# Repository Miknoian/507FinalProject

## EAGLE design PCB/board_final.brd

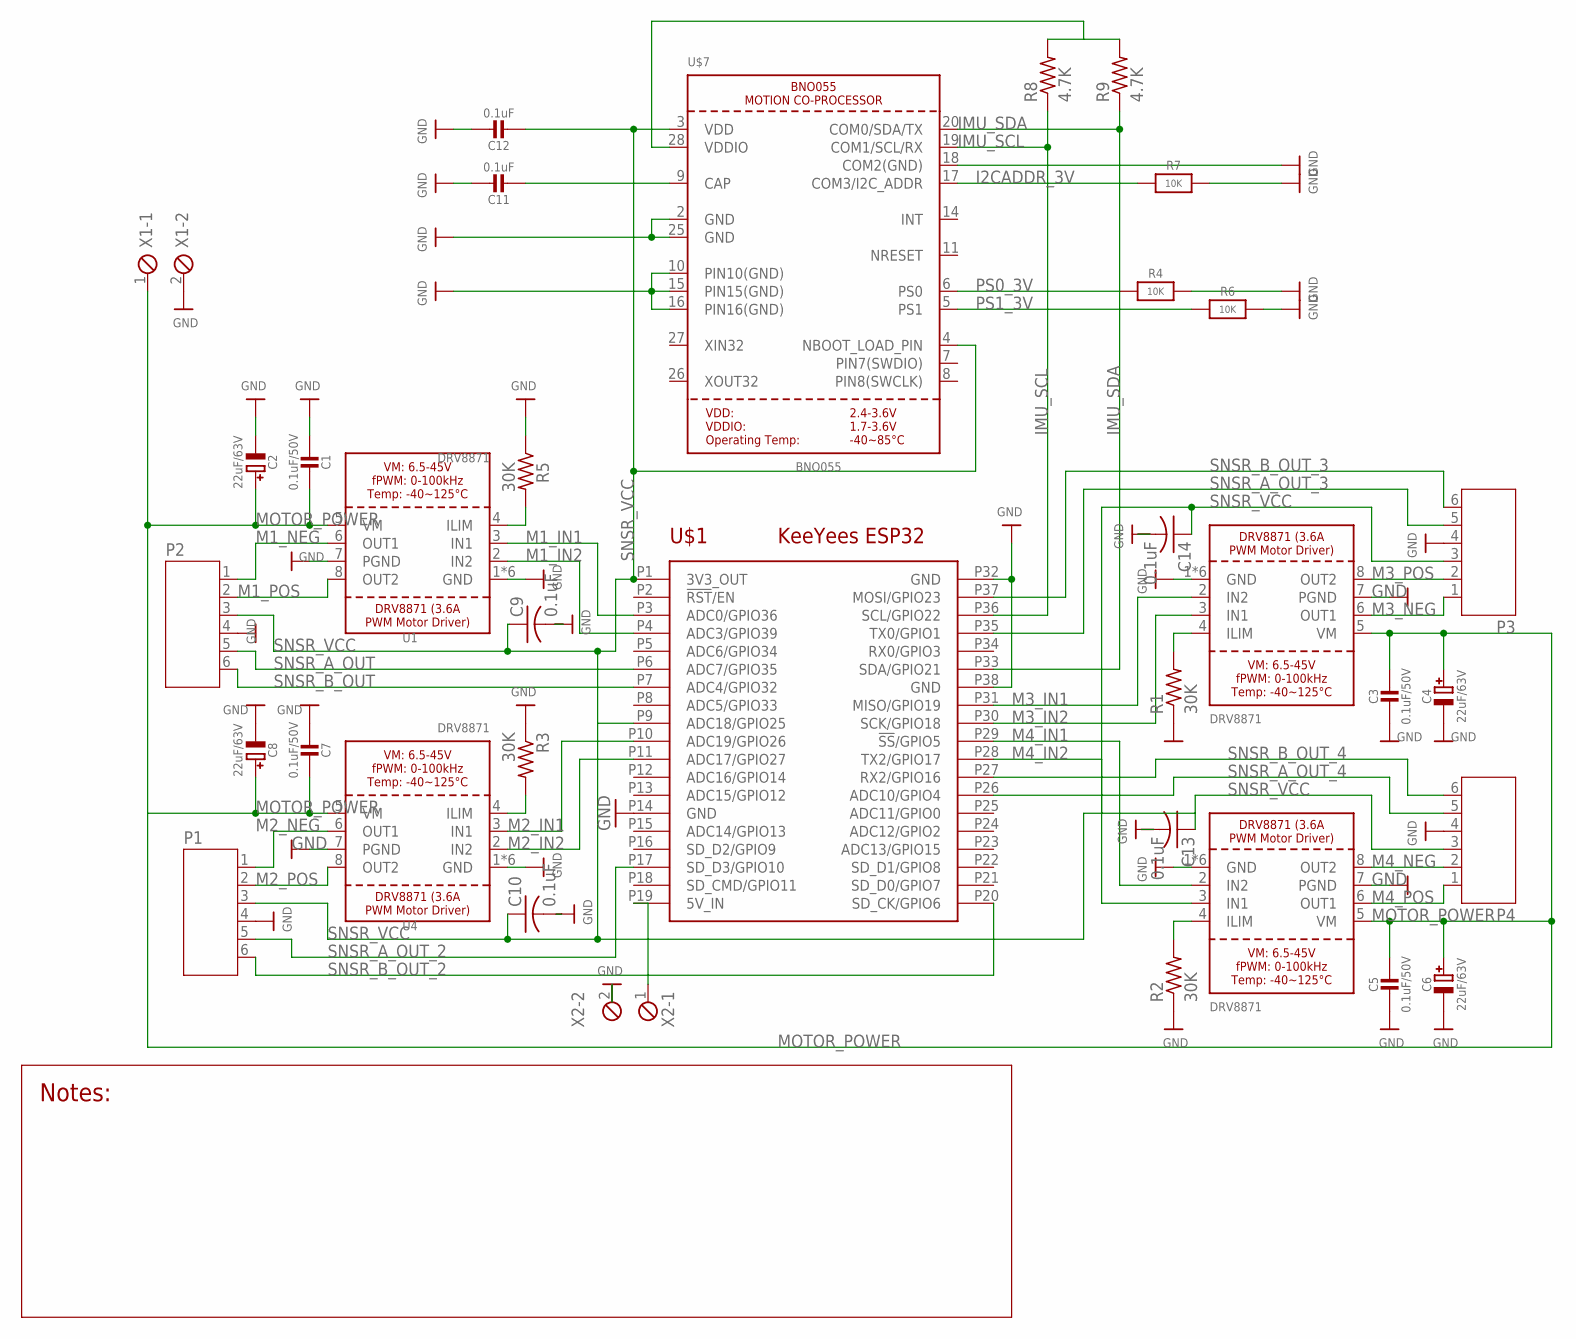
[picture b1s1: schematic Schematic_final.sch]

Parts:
C1, C3, C5, C7: 0.1uF/50V; 0805-NO
C2, C4, C6, C8: 22uF/63V; PANASONIC_D
C9, C10, C13, C14: 0.1uF; C025-030X050
C11: 0.1uF; 0805-NO
C12: 0.1uF; 0805_10MGAP
P1, P2, P3, P4: JST-PH6
R1, R2, R3, R5: 30K; 0805-THM
R4, R6, R7: 10K; 0805-NO
R8, R9: 4.7K; R0805
U1, U2, U3, U4: DRV8871; HSOP8
U$1: KEEYEES_ESP32
U$7: BNO055
X1, X2: SCREWTERM_2P_254; 2POL254

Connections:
ESP_PWR: U$1.P19 (5V_IN), X2.1
GND: C1.2, C2.-, C3.2, C4.-, C5.2, C6.-, C7.2, C8.-, C9.2, C10.2, C11.1, C12.1, C13.2, C14.2, P1.4, P2.4, P3.4, P4.4, R1.1, R2.1, R3.1, R4.2, R5.1, R6.2, R7.2, U1.1 (GND), U1.7 (PGND), U1.GND, U1.P$1 (GND), U1.P$2 (GND), U1.P$3 (GND), U1.P$4 (GND), U2.1 (GND), U2.7 (PGND), U2.GND, U2.P$1 (GND), U2.P$2 (GND), U2.P$3 (GND), U2.P$4 (GND), U3.1 (GND), U3.7 (PGND), U3.GND, U3.P$1 (GND), U3.P$2 (GND), U3.P$3 (GND), U3.P$4 (GND), U4.1 (GND), U4.7 (PGND), U4.GND, U4.P$1 (GND), U4.P$2 (GND), U4.P$3 (GND), U4.P$4 (GND), U$1.P14 (GND), U$1.P32 (GND), U$1.P38 (GND), U$7.2 (GND), U$7.10 (PIN10(GND)), U$7.15 (PIN15(GND)), U$7.16 (PIN16(GND)), U$7.18 (COM2(GND)), U$7.25 (GND), X1.2, X2.2
I2CADDR_3V: R7.1, U$7.17 (COM3/I2C_ADDR)
IMU_SCL: R8.1, U$1.P36 (SCL/GPIO22), U$7.19 (COM1/SCL/RX)
IMU_SDA: R9.1, U$1.P33 (SDA/GPIO21), U$7.20 (COM0/SDA/TX)
M1_IN1: U1.3 (IN1), U$1.P3 (ADC0/GPIO36)
M1_IN2: U1.2 (IN2), U$1.P4 (ADC3/GPIO39)
M1_NEG: P2.1, U1.6 (OUT1)
M1_POS: P2.2, U1.8 (OUT2)
M2_IN1: U4.3 (IN1), U$1.P10 (ADC19/GPIO26)
M2_IN2: U4.2 (IN2), U$1.P11 (ADC17/GPIO27)
M2_NEG: P1.1, U4.6 (OUT1)
M2_POS: P1.2, U4.8 (OUT2)
M3_IN1: U2.2 (IN2), U$1.P31 (MISO/GPIO19)
M3_IN2: U2.3 (IN1), U$1.P30 (SCK/GPIO18)
M3_NEG: P3.1, U2.6 (OUT1)
M3_POS: P3.2, U2.8 (OUT2)
M4_IN1: U3.2 (IN2), U$1.P29 (!SS!/GPIO5)
M4_IN2: U3.3 (IN1), U$1.P28 (TX2/GPIO17)
M4_NEG: P4.2, U3.8 (OUT2)
M4_POS: P4.1, U3.6 (OUT1)
MOTOR_POWER: C1.1, C2.+, C3.1, C4.+, C5.1, C6.+, C7.1, C8.+, U1.5 (VM), U2.5 (VM), U3.5 (VM), U4.5 (VM), X1.1
unnamed: R1.2, U2.4 (ILIM)
unnamed: R2.2, U3.4 (ILIM)
unnamed: R3.2, U4.4 (ILIM)
unnamed: R8.2, R9.2, U$7.28 (VDDIO)
unnamed: C11.2, U$7.9 (CAP)
unnamed: R5.2, U1.4 (ILIM)
PS0_3V: R4.1, U$7.6 (PS0)
PS1_3V: R6.1, U$7.5 (PS1)
SNSR_A_OUT: P2.5, U$1.P6 (ADC7/GPIO35)
SNSR_A_OUT_2: P1.5, U$1.P17 (SD_D3/GPIO10)
SNSR_A_OUT_3: P3.5, U$1.P35 (TX0/GPIO1)
SNSR_A_OUT_4: P4.5, U$1.P26 (ADC10/GPIO4)
SNSR_B_OUT: P2.6, U$1.P7 (ADC4/GPIO32)
SNSR_B_OUT_2: P1.6, U$1.P20 (SD_CK/GPIO6)
SNSR_B_OUT_3: P3.6, U$1.P37 (MOSI/GPIO23)
SNSR_B_OUT_4: P4.6, U$1.P27 (RX2/GPIO16)
SNSR_VCC: C9.1, C10.1, C12.2, C13.1, C14.1, P1.3, P2.3, P3.3, P4.3, U$1.P1 (3V3_OUT), U$7.3 (VDD), U$7.4 (NBOOT_LOAD_PIN)

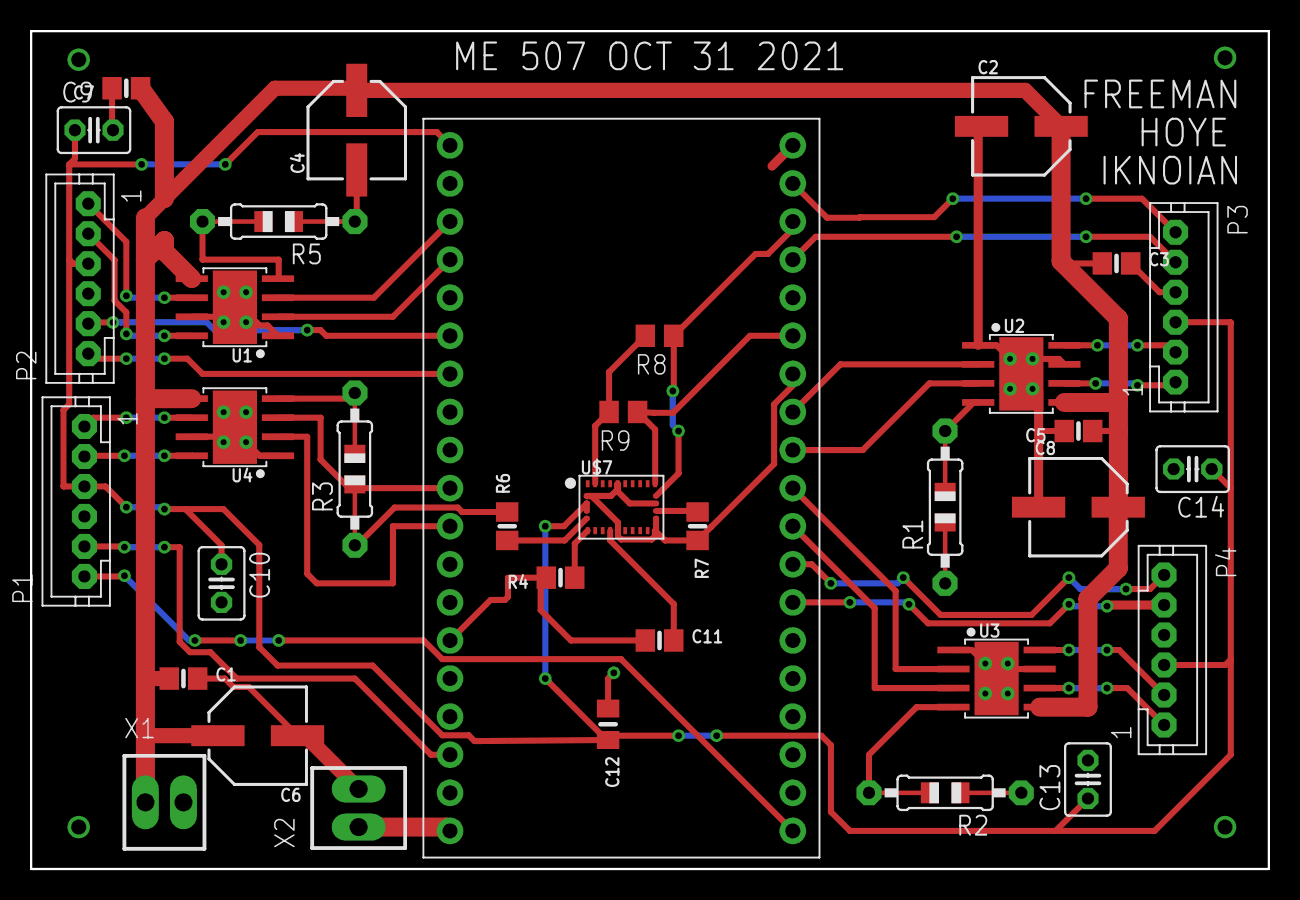
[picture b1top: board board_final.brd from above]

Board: 2 copper layers, 82.5 x 55.9 mm, 35 parts (0 on the bottom side), 39 nets.

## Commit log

2021-11-30 commintinzinng codes
2021-11-30 Update main.cpp
    Important comments
2021-12-01 Added files for the motor driver class
2021-12-01 Small changes to motor class
2021-12-01 added a space to the print line
2021-12-01 WiFi Addition
2021-12-01 First motor task upload
2021-12-01 Controller function with direction functionality.
    Controller function takes a direction input and creates a scaler for the desired speed on each motor. This will then be multiplied by the desired overall nominal speed to get the nominal speed for ea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
2021-12-01 Updated controller function. Still needs work.
2021-12-01 WiFiTasks
2021-12-01 Moved variable declarations
2021-12-01 Added WiFi Task
2021-12-02 Fixed 507 library issues
2021-12-02 Added motor tasks
    Also commented out wifi task because it crashes without the external capacitors.
2021-12-02 Attempting WiFi again
2021-12-02 Made encoder highest priority
2021-12-02 Decreased encoder period
2021-12-02 Added comment about what should be in setup
2021-12-02 Idk but this apparently changed
2021-12-02 Started implementing pulling shares
2021-12-02 WiFi Attempt
2021-12-02 Updated encoder pins
2021-12-02 Changed controller to task
2021-12-02 WiFi Fixed Finally
2021-12-02 YEEEET
2021-12-02 Controller shares update
2021-12-02 Revert "Merge branch 'master' of https://github.com/Miknoian/507FinalProject"
    This reverts commit a5a486d87d95e114b057af5a317e0b058c07fcfe, reversing
    changes made to 4deb03926c52c2ed0cce40e48a75878d3fa8a432.
2021-12-02 Changes to Wifi shares and motor task
2021-12-02 Client isnt connecting
    Client is not connecting but wifi doesnt crash. Motor task takes magnitude for PWM. Need to implement controller task
2021-12-05 Starting to make controller functional
2021-12-06 Implemented untested controller
2021-12-06 Added app .apk file
2021-12-06 Angle write update
    Angles are now correctly expressed as 0-360 + minor task changes
2021-12-06 Working controller
2021-12-06 Most recent update
2021-12-06 Thorough documentation overhaul
2021-12-07 Changed vTaskDelay to 100ms
    Updated delay will produce much more accurate velocity results at low speed. There is probably some balance between encoder response time and velocity accuracy (granularity?)
2021-12-07 Added PCB CAD
2021-12-07 Added motor datasheet
2021-12-07 Doxygen
2021-12-08 Documentation Changes
2021-12-08 Added derivative
2021-12-08 Controller finalized
2021-12-08 About to mess things up so quicksaving
2021-12-08 Documentation
2021-12-08 Documentation
    updated comments, doxy
2021-12-08 task comments
2021-12-08 doxy site
2021-12-09 forgot to save, final control scheme

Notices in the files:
parts and their libraries:
microbuilder: This work is placed in the public domain, and may be freely used for commercial and non-commercial work with the following conditions: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
